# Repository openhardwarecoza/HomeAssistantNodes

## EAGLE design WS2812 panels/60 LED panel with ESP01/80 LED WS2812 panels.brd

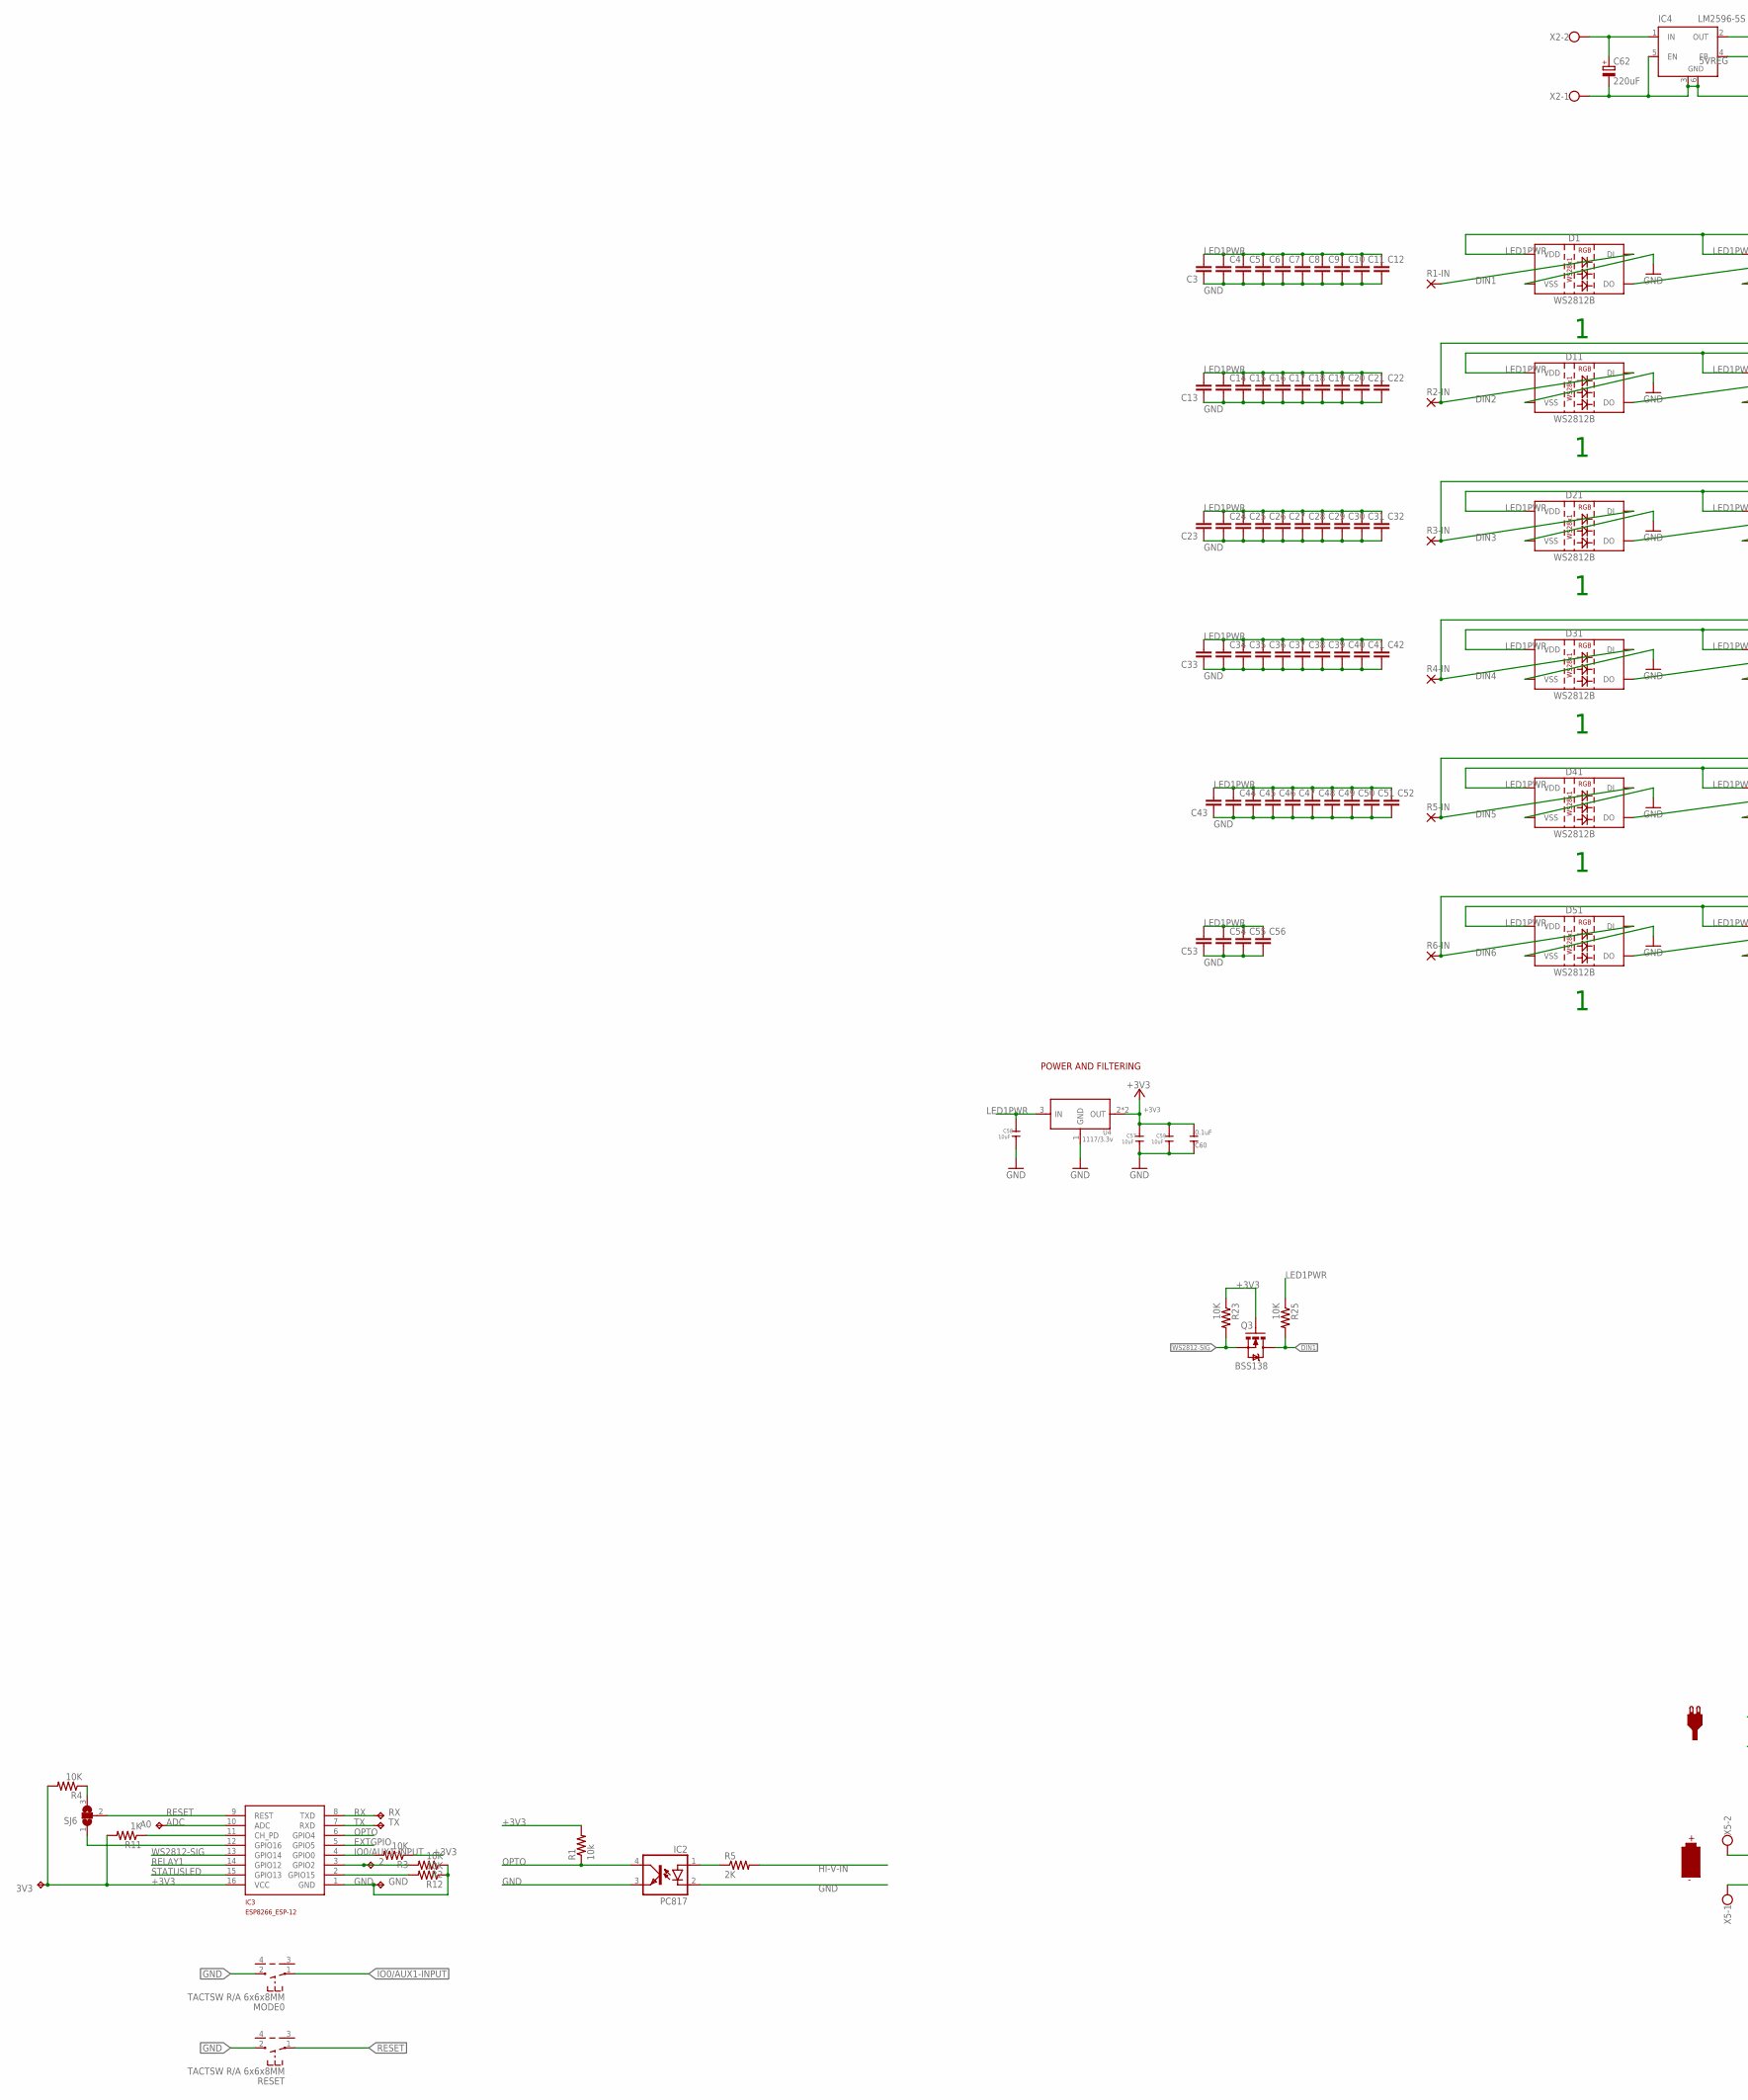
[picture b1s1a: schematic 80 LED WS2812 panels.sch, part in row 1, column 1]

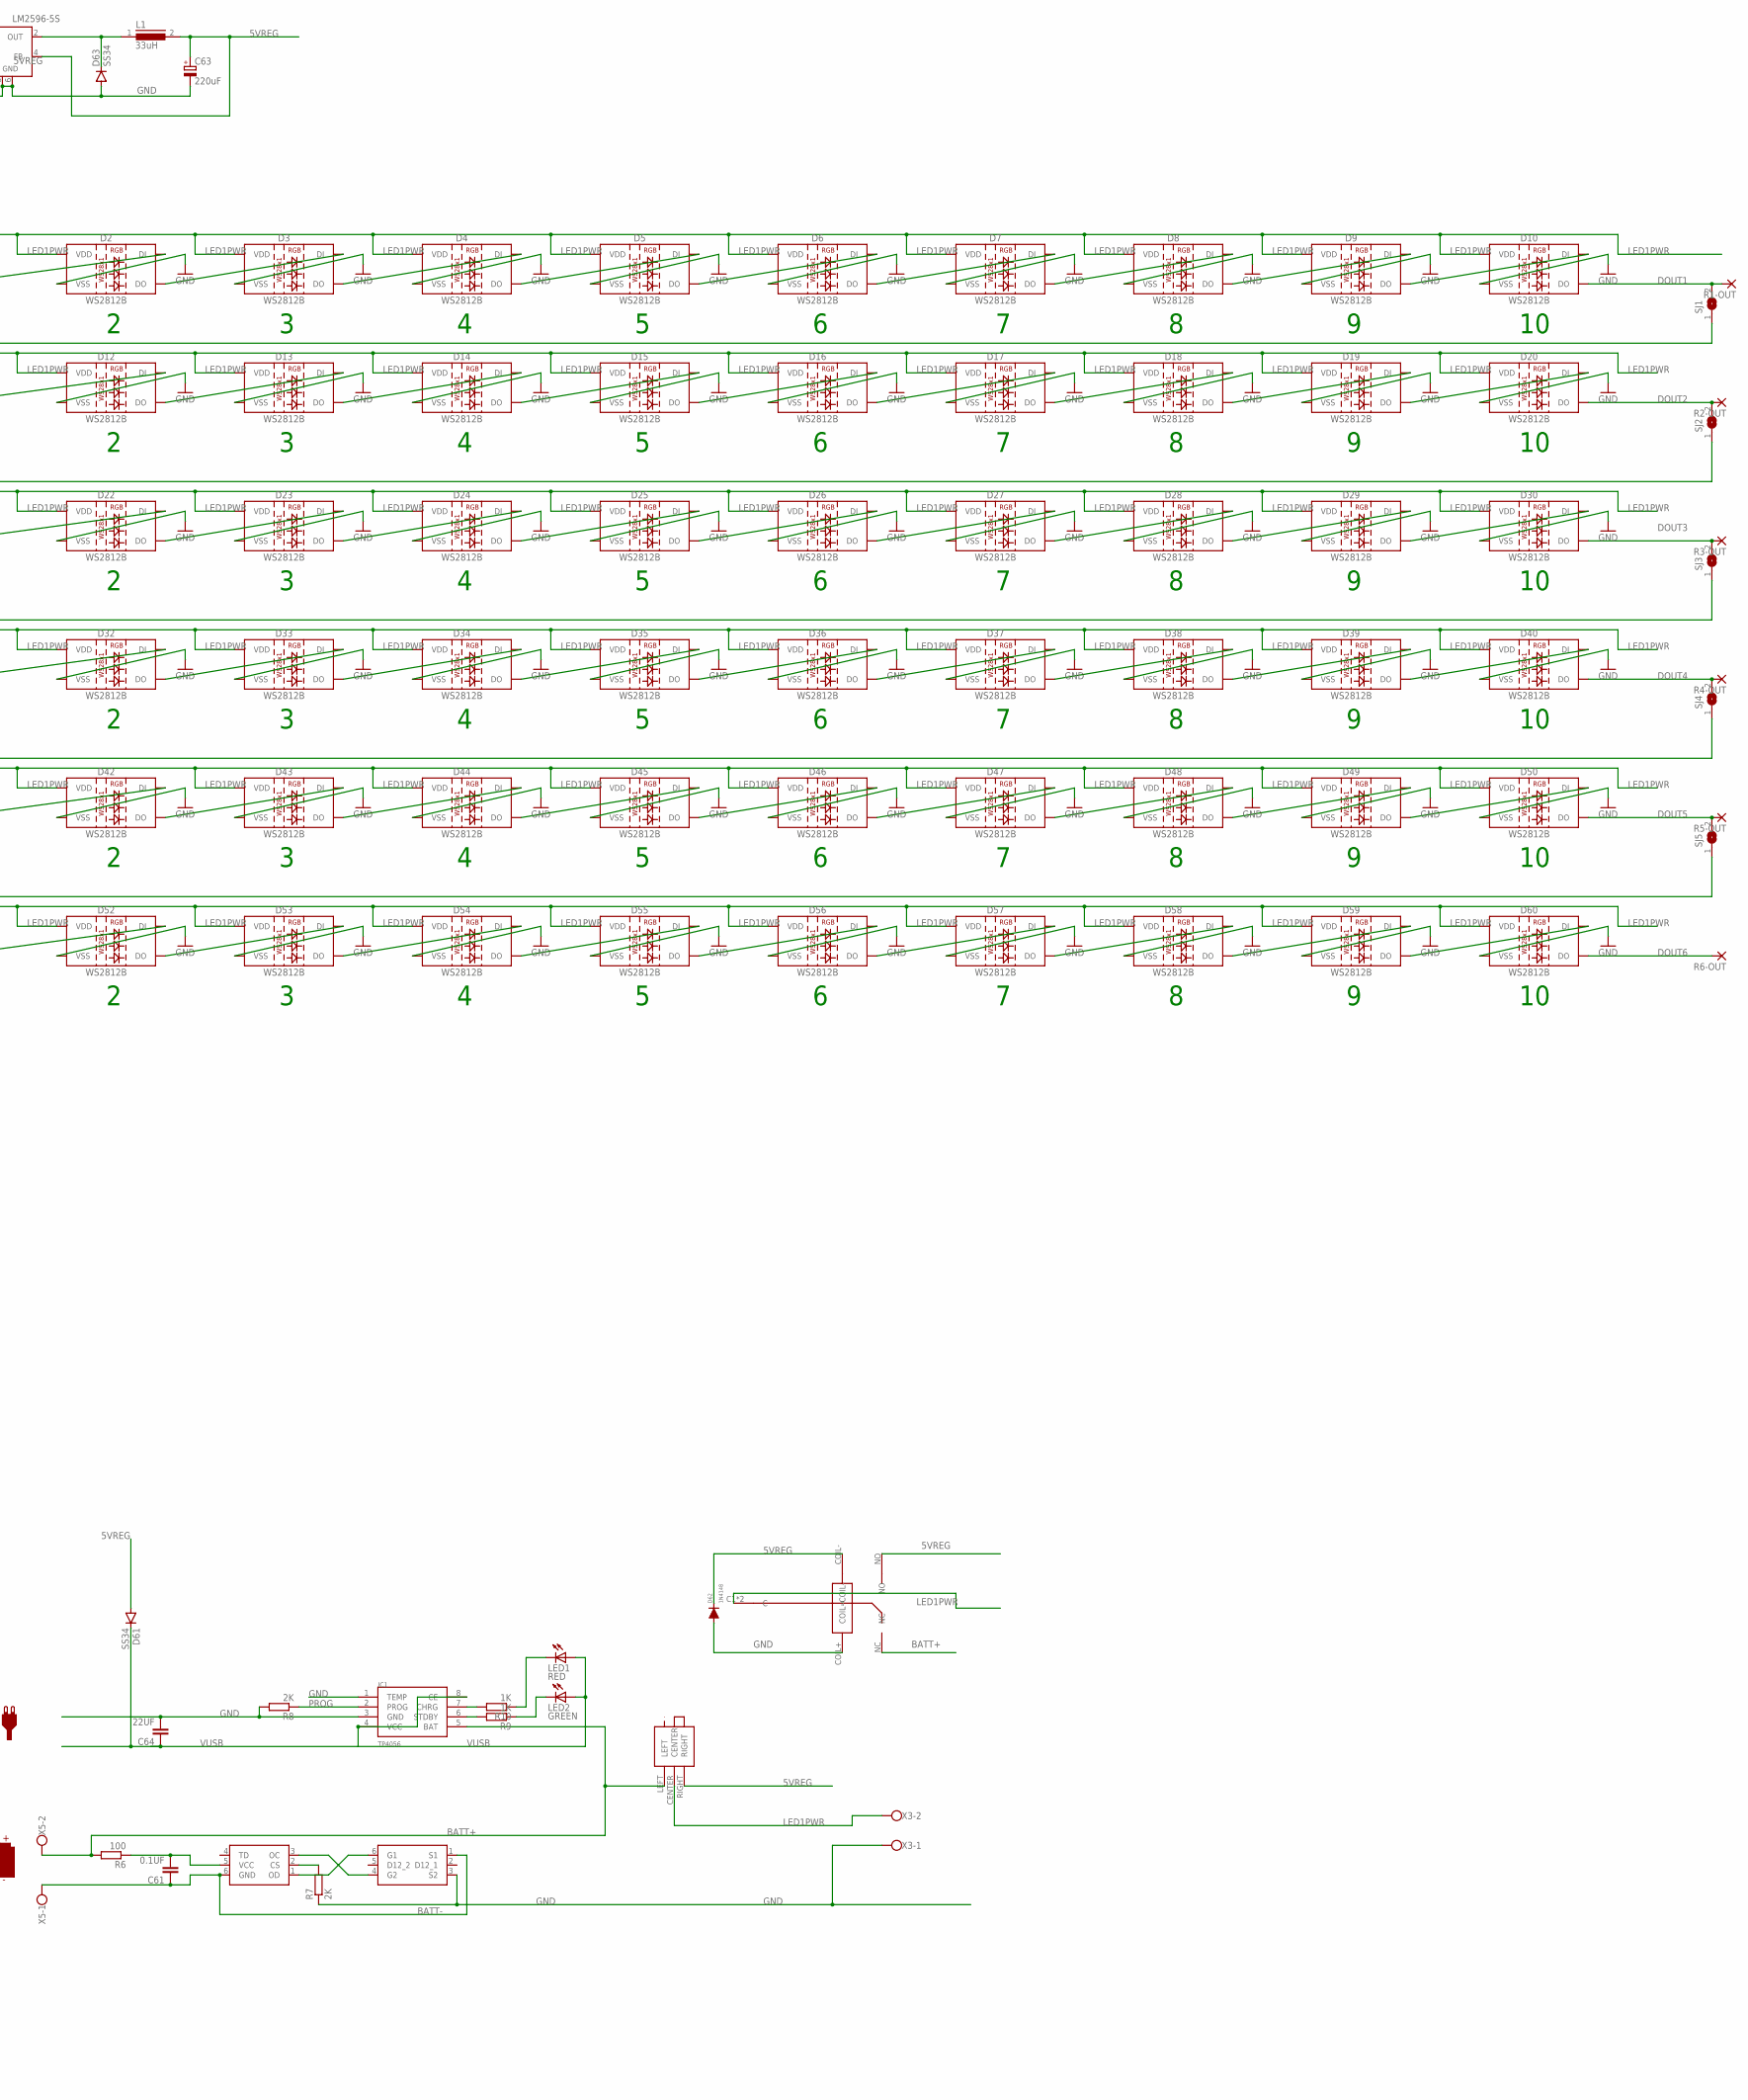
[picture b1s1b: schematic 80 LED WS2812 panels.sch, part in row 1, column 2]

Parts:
2, 3V3: TPTP13SQ; TP13SQ
A0: TPTP13SQ; TP13SQ
C3, C4, C5, C6, C7, C8, C9, C10, C11, C12, C13, C14, C15, C16, C17, C18, C19, C20, C21, C22, C23, C24, C25, C26, C27, C28, C29, C30, C31, C32, C33, C34, C35, C36, C37, C38, C39, C40, C41, C42, C43, C44, C45, C46, C47, C48, C49, C50, C51, C52, C53, C54, C55, C56: C-EUC1206; C1206@1
C57, C58, C59: 10uF; C1206
C60: 0.1uF; DISCRETE_C1206
C61: 0.1UF; C1206@1
C62, C63: 220uF; E3,5-10
C64: 22UF; C1812K@1
D1, D2, D3, D4, D5, D6, D7, D8, D9, D10, D11, D12, D13, D14, D15, D16, D17, D18, D19, D20, D21, D22, D23, D24, D25, D26, D27, D28, D29, D30, D31, D32, D33, D34, D35, D36, D37, D38, D39, D40, D41, D42, D43, D44, D45, D46, D47, D48, D49, D50, D51, D52, D53, D54, D55, D56, D57, D58, D59, D60: WS2812B
D61, D63: SS34; DO-214AC
D62: 1N4148; SOD-323
GND: TPTP13SQ; TP13SQ
IC1: TP4056; SOP-8
IC2: PC817; DIL04
IC3: ESP8266_ESP-12; ESP8266-ESP12
IC4: LM2596-5S; TO263-5
L1: 33uH; DR127
LED1: RED; LED3MM
LED2: GREEN; LED3MM
MODE0: TACTSW R/A 6x6x8MM; SW_TACT_STANDARD_RIGHT_ANGLE
Q3: BSS138; SOT23-3
R1: 10k; R1206
R1-IN, R1-OUT, R2-IN, R2-OUT, R3-IN, R3-OUT, R4-IN, R4-OUT, R5-IN, R5-OUT, R6-IN, R6-OUT: 2,15/1,0
R2, R3, R4, R12: 10K; R1206
R5, R7, R8: 2K; R1206
R6: 100; R1206
R9, R10, R11: 1K; R1206
R23, R25: 10K; 1206
RESET: TACTSW R/A 6x6x8MM; SW_TACT_STANDARD_RIGHT_ANGLE
RX: TPTP13SQ; TP13SQ
SJ1, SJ2, SJ3, SJ4, SJ5: SJ
SJ6: SJ2W; SJ_2
TX: TPTP13SQ; TP13SQ
U4: 1117/3.3v; SOT-223
U$1: FS312F-G; SOT23-6
U$2: FS8205; SOT23-6
U$3: XKBENTERPRISESS-12D11G5R
U$13: JRC-21F-4100
X2, X3, X5: W237-102

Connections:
5VREG: C63.+, D61.A, D62.C, IC4.4 (FB), L1.2, U$3.RIGHT, U$13.COIL-, U$13.NO
+3V3: 3V3.TP, C57.1, C59.1, C60.2, IC3.16 (VCC), Q3.1 (G), R1.2, R3.1, R4.2, R11.2, R23.1, U4.2 (OUT), U4.TER (OUT)
ADC: A0.TP, IC3.10 (ADC)
BATT+: IC1.5 (BAT), R6.2, U$3.LEFT, U$13.NC, X5.2
BATT-: C61.1, U$1.6 (GND), U$2.1 (S1), X5.1
CHG: IC1.7 (CHRG), R10.2
DIN1: D1.4 (DI), Q3.3 (D), R1-IN.1, R25.2
DIN2: D11.4 (DI), R2-IN.1, SJ1.1
DIN3: D21.4 (DI), R3-IN.1, SJ2.1
DIN4: D31.4 (DI), R4-IN.1, SJ3.1
DIN5: D41.4 (DI), R5-IN.1, SJ4.1
DIN6: D51.4 (DI), R6-IN.1, SJ5.1
DOUT1: D10.2 (DO), R1-OUT.1, SJ1.2
DOUT2: D20.2 (DO), R2-OUT.1, SJ2.2
DOUT3: D30.2 (DO), R3-OUT.1, SJ3.2
DOUT4: D40.2 (DO), R4-OUT.1, SJ4.2
DOUT5: D50.2 (DO), R5-OUT.1, SJ5.2
DOUT6: D60.2 (DO), R6-OUT.1
EXTGPIO: IC3.5 (GPIO5)
GND: C3.1, C4.2, C5.2, C6.2, C7.2, C8.2, C9.2, C10.2, C11.2, C12.2, C13.1, C14.2, C15.2, C16.2, C17.2, C18.2, C19.2, C20.2, C21.2, C22.2, C23.1, C24.2, C25.2, C26.2, C27.2, C28.2, C29.2, C30.2, C31.2, C32.2, C33.1, C34.2, C35.2, C36.2, C37.2, C38.2, C39.2, C40.2, C41.2, C42.2, C43.1, C44.2, C45.2, C46.2, C47.2, C48.2, C49.2, C50.2, C51.2, C52.2, C53.1, C54.2, C55.2, C56.2, C57.2, C58.2, C59.2, C60.1, C62.-, C63.-, C64.2, D1.3 (VSS), D2.3 (VSS), D3.3 (VSS), D4.3 (VSS), D5.3 (VSS), D6.3 (VSS), D7.3 (VSS), D8.3 (VSS), D9.3 (VSS), D10.3 (VSS), D11.3 (VSS), D12.3 (VSS), D13.3 (VSS), D14.3 (VSS), D15.3 (VSS), D16.3 (VSS), D17.3 (VSS), D18.3 (VSS), D19.3 (VSS), D20.3 (VSS), D21.3 (VSS), D22.3 (VSS), D23.3 (VSS), D24.3 (VSS), D25.3 (VSS), D26.3 (VSS), D27.3 (VSS), D28.3 (VSS), D29.3 (VSS), D30.3 (VSS), D31.3 (VSS), D32.3 (VSS), D33.3 (VSS), D34.3 (VSS), D35.3 (VSS), D36.3 (VSS), D37.3 (VSS), D38.3 (VSS), D39.3 (VSS), D40.3 (VSS), D41.3 (VSS), D42.3 (VSS), D43.3 (VSS), D44.3 (VSS), D45.3 (VSS), D46.3 (VSS), D47.3 (VSS), D48.3 (VSS), D49.3 (VSS), D50.3 (VSS), D51.3 (VSS), D52.3 (VSS), D53.3 (VSS), D54.3 (VSS), D55.3 (VSS), D56.3 (VSS), D57.3 (VSS), D58.3 (VSS), D59.3 (VSS), D60.3 (VSS), D62.A, D63.A, GND.TP, IC1.1 (TEMP), IC1.3 (GND), IC2.2 (C), IC2.3 (EMIT), IC3.1 (GND), IC4.3 (GND), IC4.5 (EN), IC4.6 (GND), MODE0.2, R2.1, R7.1, R8.2, R12.1, RESET.2, U4.1 (GND), U$2.3 (S2), U$13.COIL+ (COIL=), X2.1, X3.1
HI-V-IN: C62.+, IC4.1 (IN), R5.2, X2.2
IO0/AUX1-INPUT: IC3.4 (GPIO0), MODE0.1, R3.2
LED1PWR: C3.2, C4.1, C5.1, C6.1, C7.1, C8.1, C9.1, C10.1, C11.1, C12.1, C13.2, C14.1, C15.1, C16.1, C17.1, C18.1, C19.1, C20.1, C21.1, C22.1, C23.2, C24.1, C25.1, C26.1, C27.1, C28.1, C29.1, C30.1, C31.1, C32.1, C33.2, C34.1, C35.1, C36.1, C37.1, C38.1, C39.1, C40.1, C41.1, C42.1, C43.2, C44.1, C45.1, C46.1, C47.1, C48.1, C49.1, C50.1, C51.1, C52.1, C53.2, C54.1, C55.1, C56.1, C58.1, D1.1 (VDD), D2.1 (VDD), D3.1 (VDD), D4.1 (VDD), D5.1 (VDD), D6.1 (VDD), D7.1 (VDD), D8.1 (VDD), D9.1 (VDD), D10.1 (VDD), D11.1 (VDD), D12.1 (VDD), D13.1 (VDD), D14.1 (VDD), D15.1 (VDD), D16.1 (VDD), D17.1 (VDD), D18.1 (VDD), D19.1 (VDD), D20.1 (VDD), D21.1 (VDD), D22.1 (VDD), D23.1 (VDD), D24.1 (VDD), D25.1 (VDD), D26.1 (VDD), D27.1 (VDD), D28.1 (VDD), D29.1 (VDD), D30.1 (VDD), D31.1 (VDD), D32.1 (VDD), D33.1 (VDD), D34.1 (VDD), D35.1 (VDD), D36.1 (VDD), D37.1 (VDD), D38.1 (VDD), D39.1 (VDD), D40.1 (VDD), D41.1 (VDD), D42.1 (VDD), D43.1 (VDD), D44.1 (VDD), D45.1 (VDD), D46.1 (VDD), D47.1 (VDD), D48.1 (VDD), D49.1 (VDD), D50.1 (VDD), D51.1 (VDD), D52.1 (VDD), D53.1 (VDD), D54.1 (VDD), D55.1 (VDD), D56.1 (VDD), D57.1 (VDD), D58.1 (VDD), D59.1 (VDD), D60.1 (VDD), R25.1, U4.3 (IN), U$3.CENTER, U$13.C1 (C), U$13.C2 (C), X3.2
LEDCHR: LED1.K (C), R10.1
LEDSBY: LED2.K (C), R9.1
unnamed: D19.2 (DO), D20.4 (DI)
unnamed: D18.2 (DO), D19.4 (DI)
unnamed: D17.2 (DO), D18.4 (DI)
unnamed: D16.2 (DO), D17.4 (DI)
unnamed: D15.2 (DO), D16.4 (DI)
unnamed: D14.2 (DO), D15.4 (DI)
unnamed: D13.2 (DO), D14.4 (DI)
unnamed: D12.2 (DO), D13.4 (DI)
unnamed: D11.2 (DO), D12.4 (DI)
unnamed: D29.2 (DO), D30.4 (DI)
unnamed: D9.2 (DO), D10.4 (DI)
unnamed: D8.2 (DO), D9.4 (DI)
unnamed: D7.2 (DO), D8.4 (DI)
unnamed: D6.2 (DO), D7.4 (DI)
unnamed: D5.2 (DO), D6.4 (DI)
unnamed: D4.2 (DO), D5.4 (DI)
unnamed: D3.2 (DO), D4.4 (DI)
unnamed: D2.2 (DO), D3.4 (DI)
unnamed: D1.2 (DO), D2.4 (DI)
unnamed: D28.2 (DO), D29.4 (DI)
unnamed: D27.2 (DO), D28.4 (DI)
unnamed: D26.2 (DO), D27.4 (DI)
unnamed: D25.2 (DO), D26.4 (DI)
unnamed: D24.2 (DO), D25.4 (DI)
unnamed: D23.2 (DO), D24.4 (DI)
unnamed: D22.2 (DO), D23.4 (DI)
unnamed: D21.2 (DO), D22.4 (DI)
unnamed: D39.2 (DO), D40.4 (DI)
unnamed: D38.2 (DO), D39.4 (DI)
unnamed: D37.2 (DO), D38.4 (DI)
unnamed: D36.2 (DO), D37.4 (DI)
unnamed: D35.2 (DO), D36.4 (DI)
unnamed: D34.2 (DO), D35.4 (DI)
unnamed: D33.2 (DO), D34.4 (DI)
unnamed: D32.2 (DO), D33.4 (DI)
unnamed: D31.2 (DO), D32.4 (DI)
unnamed: D49.2 (DO), D50.4 (DI)
unnamed: D48.2 (DO), D49.4 (DI)
unnamed: D47.2 (DO), D48.4 (DI)
unnamed: D46.2 (DO), D47.4 (DI)
unnamed: D45.2 (DO), D46.4 (DI)
unnamed: D44.2 (DO), D45.4 (DI)
unnamed: D43.2 (DO), D44.4 (DI)
unnamed: D42.2 (DO), D43.4 (DI)
unnamed: D41.2 (DO), D42.4 (DI)
unnamed: D59.2 (DO), D60.4 (DI)
unnamed: D58.2 (DO), D59.4 (DI)
unnamed: D57.2 (DO), D58.4 (DI)
unnamed: D56.2 (DO), D57.4 (DI)
unnamed: D55.2 (DO), D56.4 (DI)
unnamed: D54.2 (DO), D55.4 (DI)
unnamed: D53.2 (DO), D54.4 (DI)
unnamed: D52.2 (DO), D53.4 (DI)
unnamed: D51.2 (DO), D52.4 (DI)
unnamed: IC2.1 (A), R5.1
unnamed: 2.TP, IC3.3 (GPIO2), R2.2
unnamed: R7.2, U$1.2 (CS)
unnamed: IC3.12 (GPIO16), SJ6.1
unnamed: IC3.11 (CH_PD), R11.1
unnamed: IC3.2 (GPIO15), R12.2
unnamed: R4.1, SJ6.3
unnamed: D63.C, IC4.2 (OUT), L1.1
OC: U$1.3 (OC), U$2.4 (G2)
OD: U$1.1 (OD), U$2.6 (G1)
OPTO: IC2.4 (COL), IC3.6 (GPIO4), R1.1
PROG: IC1.2 (PROG), R8.1
RELAY1: IC3.14 (GPIO12)
RESET: IC3.9 (REST), RESET.1, SJ6.2
RX: IC3.8 (TXD), RX.TP
STANDBY: IC1.6 (STDBY), R9.2
STATUSLED: IC3.15 (GPIO13)
TX: IC3.7 (RXD), TX.TP
VCC-PROT: C61.2, R6.1, U$1.5 (VCC)
VUSB: C64.1, D61.C, IC1.4 (VCC), IC1.8 (CE), LED1.A, LED2.A
WS2812-SIG: IC3.13 (GPIO14), Q3.2 (S), R23.2

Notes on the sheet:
POWER AND FILTERING

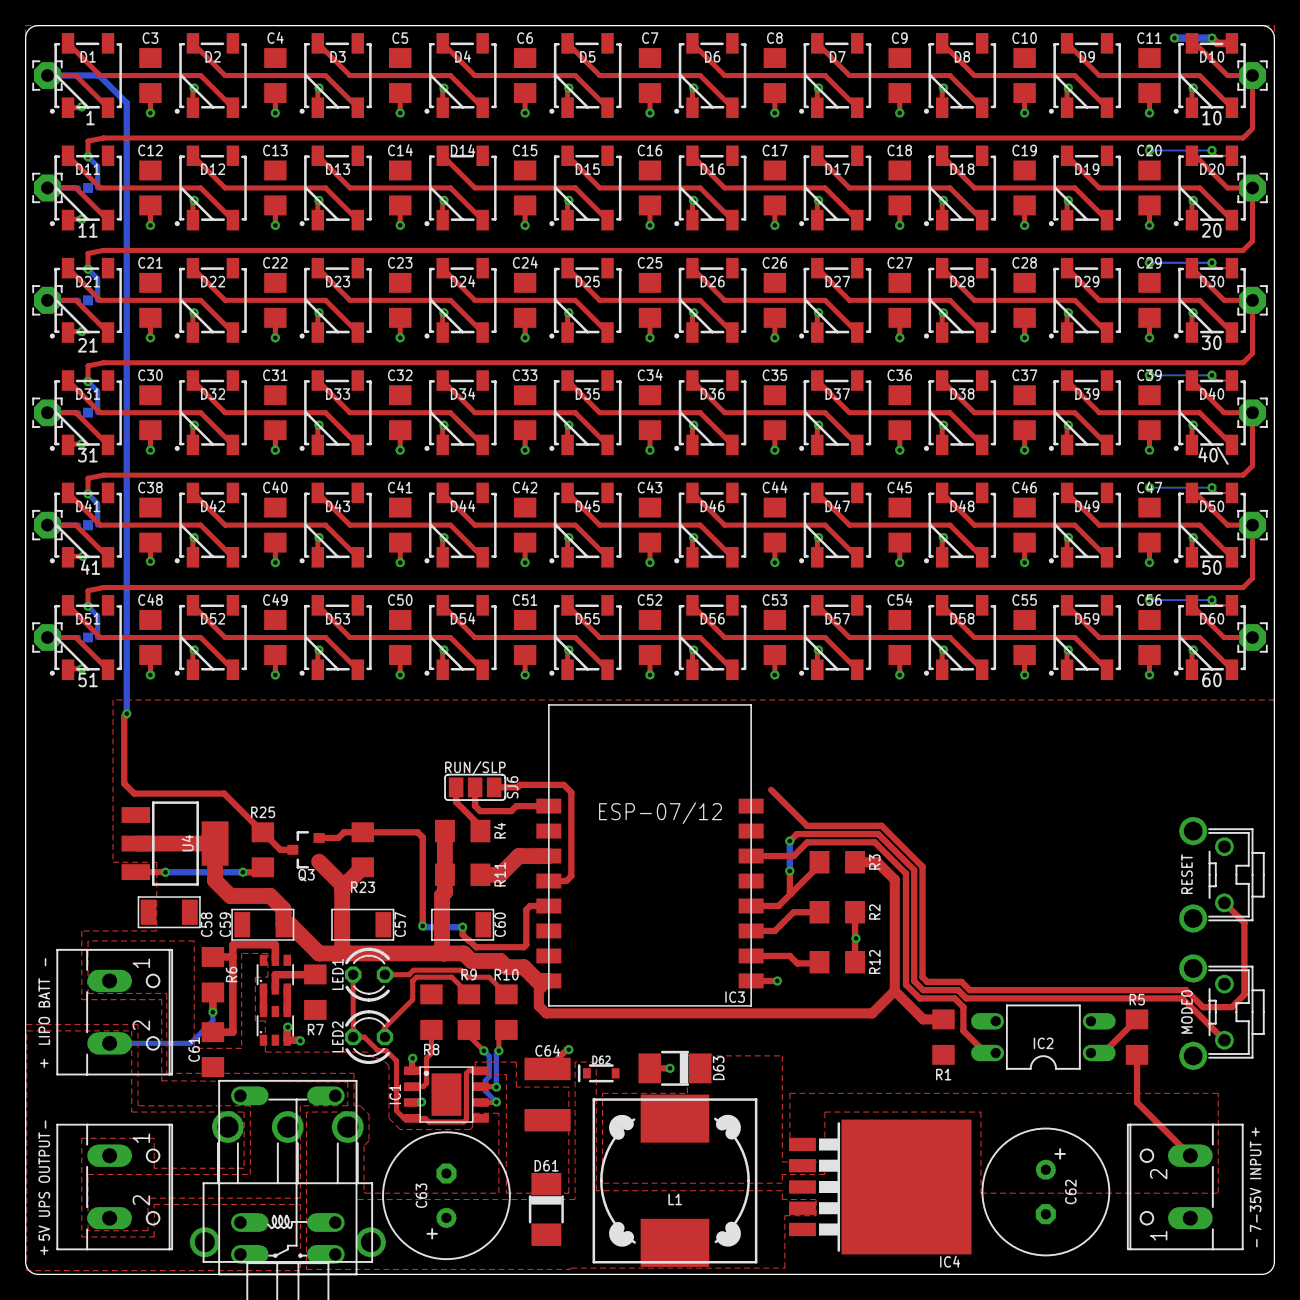
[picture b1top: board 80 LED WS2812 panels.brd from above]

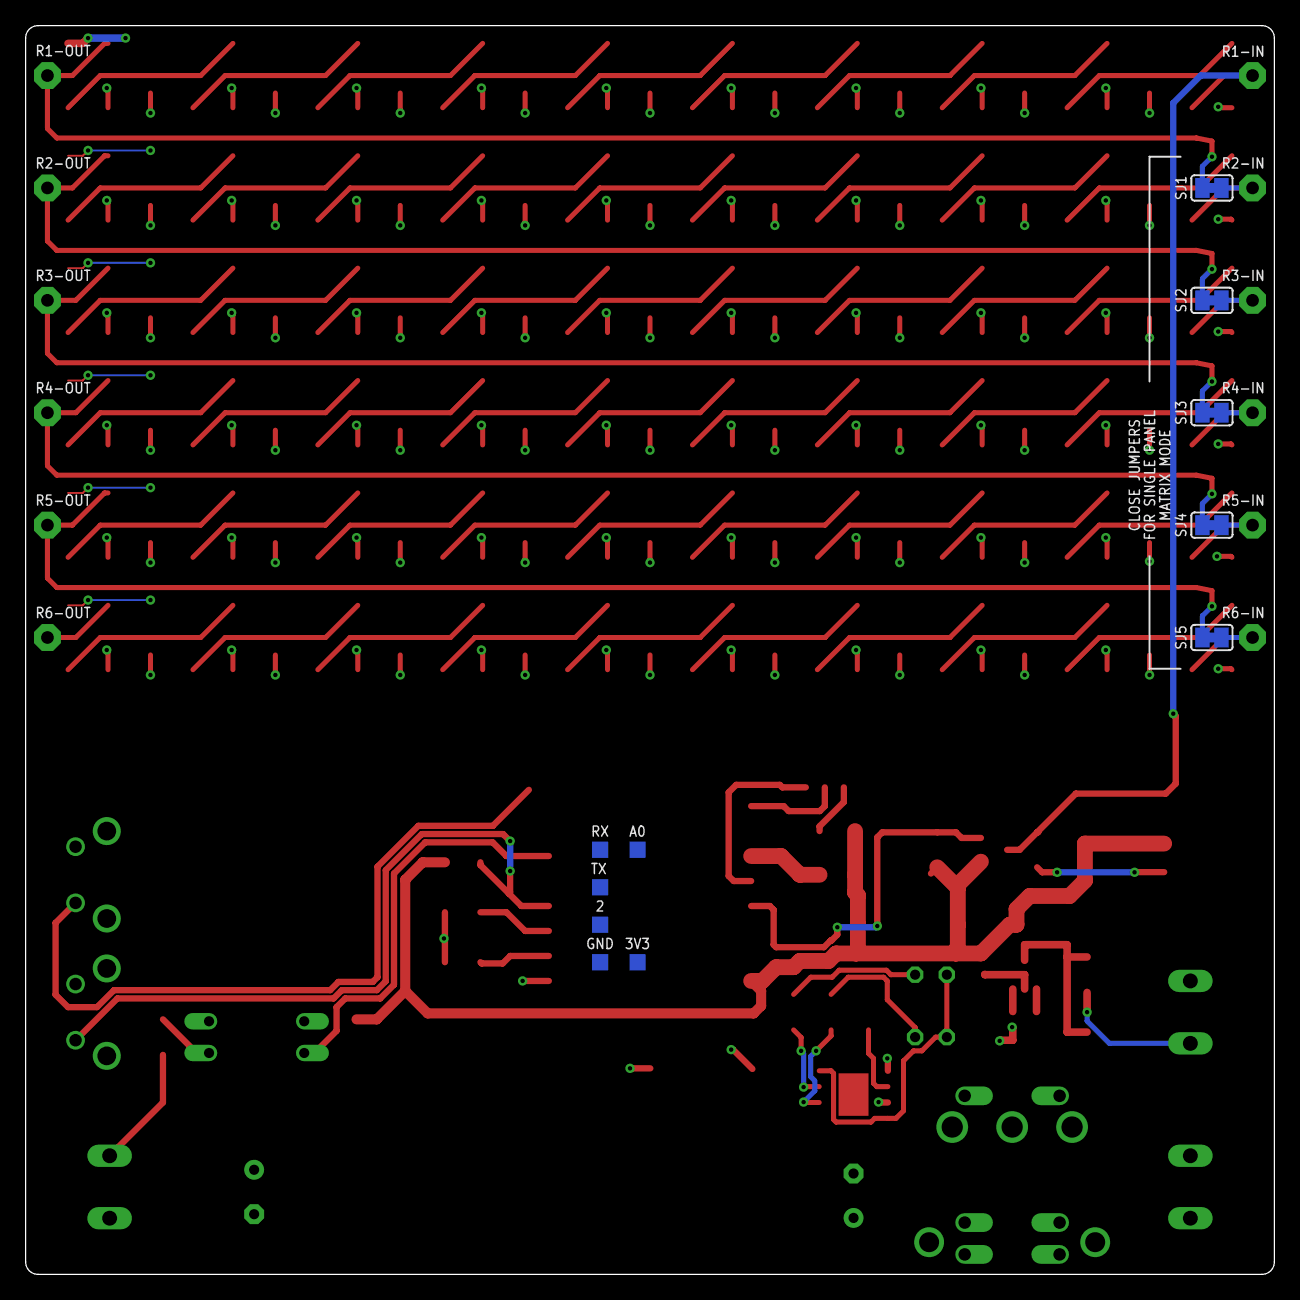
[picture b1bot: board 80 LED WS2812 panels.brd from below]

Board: 2 copper layers, 100.0 x 100.0 mm, 181 parts (11 on the bottom side), 97 nets.

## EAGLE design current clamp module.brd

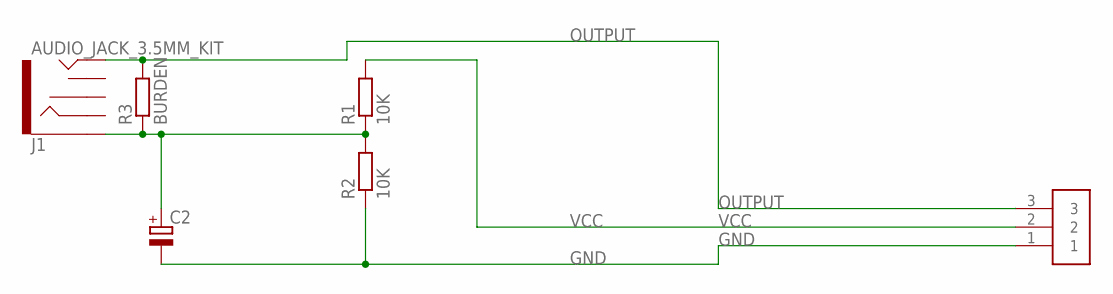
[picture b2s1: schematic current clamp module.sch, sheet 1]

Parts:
ACCURR\: Phoenix Pluggable 3.81mm 3 way; 3.81MM-3WAY-PLUGGABLE-SCREW
C2: CPOL-EUE2.5-6; E2,5-6
J1: AUDIO_JACK_3.5MM_KIT; AUDIO-JACK-KIT
R1, R2: 10K; M1206
R3: BURDEN; M1206

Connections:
GND: ACCURR\.1, C2.-, R2.1; also elsewhere on the board
unnamed: C2.+, J1.SLEEVE, R1.1, R2.2, R3.1
OUTPUT: ACCURR\.3, J1.TIP, R3.2
VCC: ACCURR\.2, R1.2

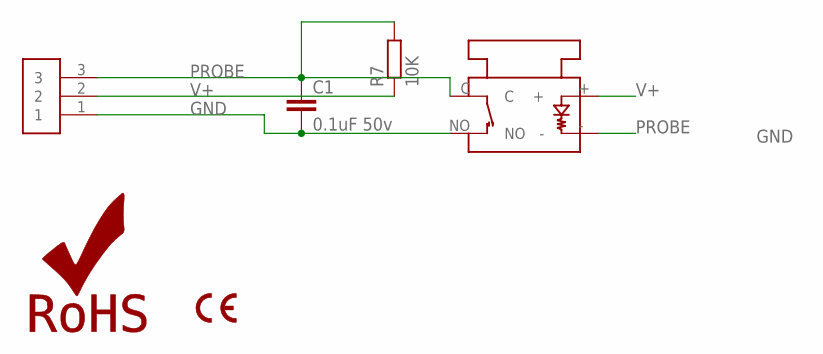
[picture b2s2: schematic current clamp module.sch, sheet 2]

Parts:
C1: 0.1uF 50v; C1206
LOGO1: ROHS_LOGO; ROHS_LOGO_0.18_IN
LOGO2: CE-4MM
PROBE: Phoenix Pluggable 3.81mm 3 way; 3.81MM-3WAY-PLUGGABLE-SCREW
R7: 10K; M1206
U$1: 25MMVANDALSWITCH

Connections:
GND: C1.2, PROBE.1, U$1.NO; also elsewhere on the board
PROBE: C1.1, PROBE.3, R7.2, U$1.-, U$1.C
V+: PROBE.2, R7.1, U$1.+

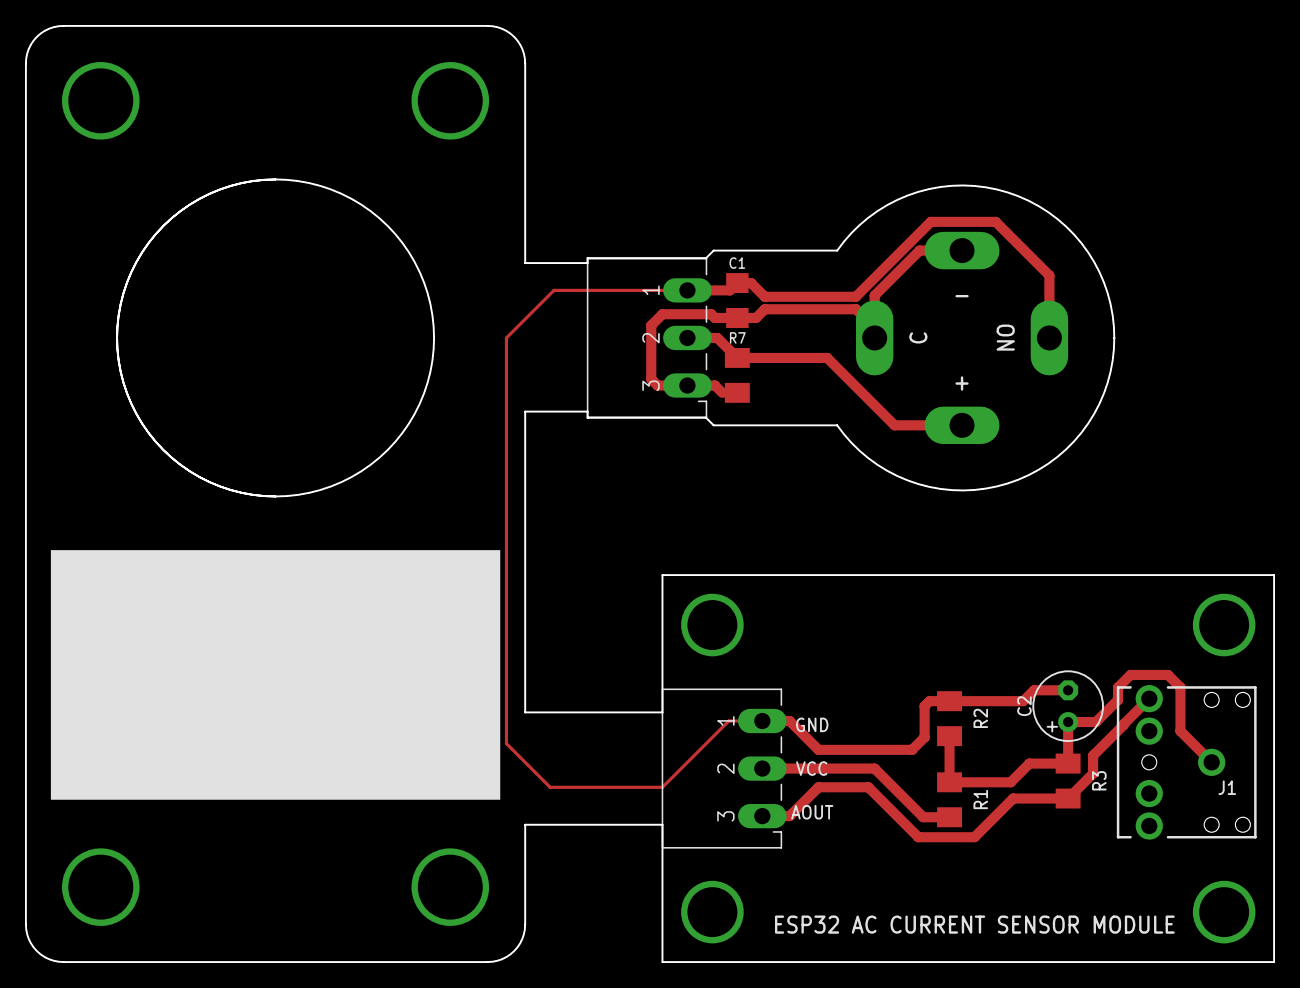
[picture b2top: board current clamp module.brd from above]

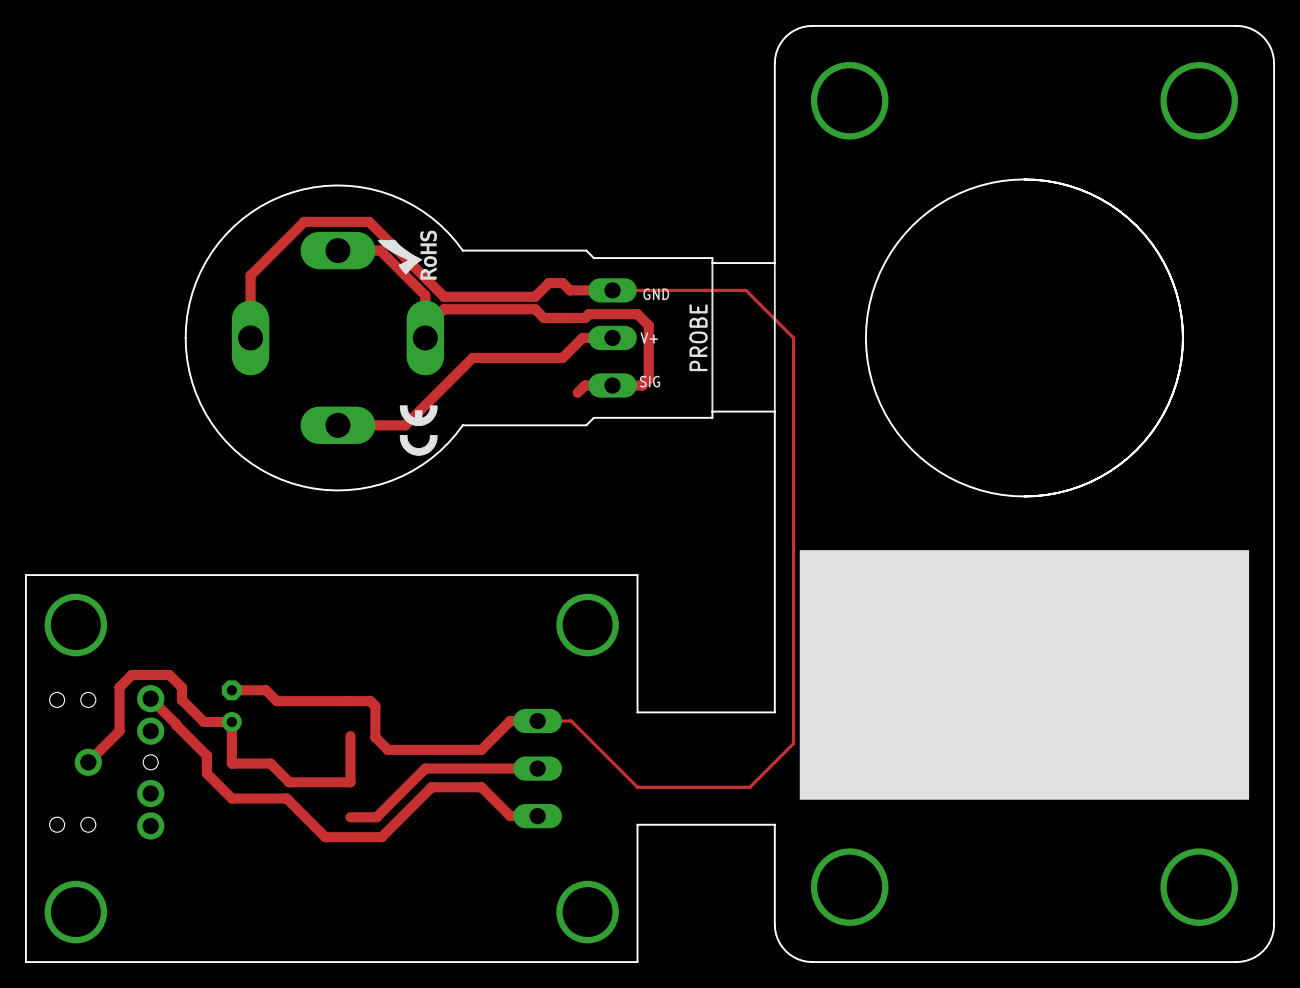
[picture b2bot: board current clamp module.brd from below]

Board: 2 copper layers, 100.0 x 75.0 mm, 12 parts (2 on the bottom side), 6 nets.

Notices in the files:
parts and their libraries:
SparkFun-LED: Licensing: Creative Commons ShareAlike 4.0 International - https://creativecommons.org/licenses/by-sa/4.0
